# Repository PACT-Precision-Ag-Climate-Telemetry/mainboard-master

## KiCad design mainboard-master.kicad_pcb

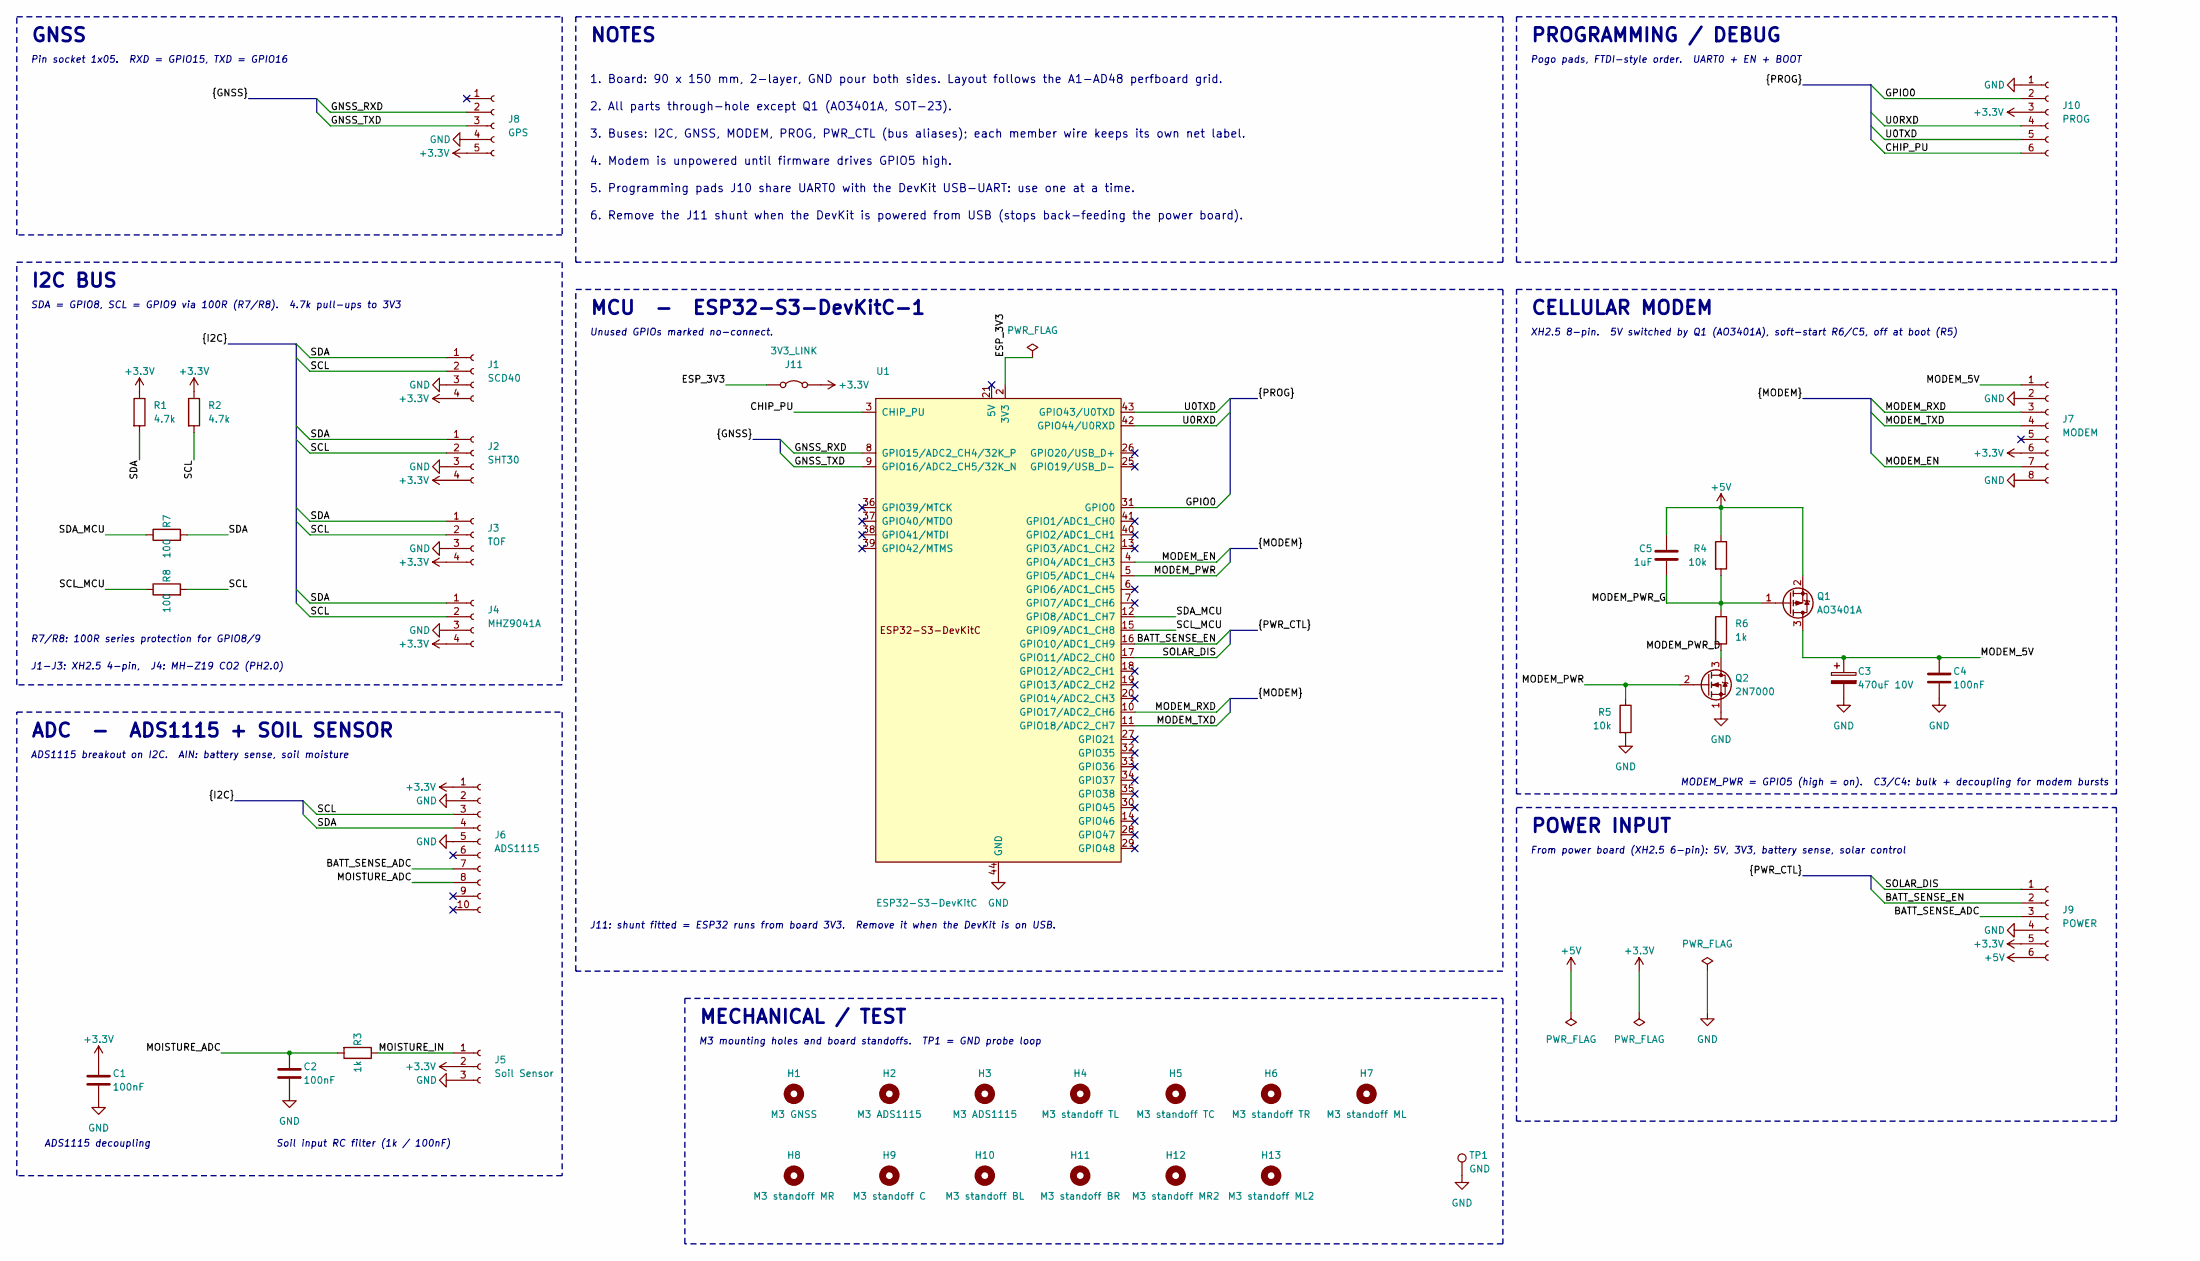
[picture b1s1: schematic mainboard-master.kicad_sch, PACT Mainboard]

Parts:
C1, C2: 100nF; C_Disc_D5.0mm_W2.5mm_P5.00mm
C3: 470uF 10V; CP_Radial_D8.0mm_P3.50mm
C4: 100nF; C_Disc_D3.0mm_W2.0mm_P2.50mm
C5: 1uF; C_Disc_D3.0mm_W2.0mm_P2.50mm
H1: M3 GNSS; MountingHole_3.2mm_M3
H2, H3: M3 ADS1115; MountingHole_3.2mm_M3
H4: M3 standoff TL; MountingHole_3.2mm_M3
H5: M3 standoff TC; MountingHole_3.2mm_M3
H6: M3 standoff TR; MountingHole_3.2mm_M3
H7: M3 standoff ML; MountingHole_3.2mm_M3
H8: M3 standoff MR; MountingHole_3.2mm_M3
H9: M3 standoff C; MountingHole_3.2mm_M3
H10: M3 standoff BL; MountingHole_3.2mm_M3
H11: M3 standoff BR; MountingHole_3.2mm_M3
H12: M3 standoff MR2; MountingHole_3.2mm_M3
H13: M3 standoff ML2; MountingHole_3.2mm_M3
J1: SCD40; JST_XH_B4B-XH-A_1x04_P2.50mm_Vertical
J2: SHT30; JST_XH_B4B-XH-A_1x04_P2.50mm_Vertical
J3: TOF; JST_XH_B4B-XH-A_1x04_P2.50mm_Vertical
J4: MHZ9041A; JST_PH_B4B-PH-K_1x04_P2.00mm_Vertical
J5: Soil Sensor; JST_XH_B3B-XH-A_1x03_P2.50mm_Vertical
J6: ADS1115; PinSocket_1x10_P2.54mm_Vertical
J7: MODEM; JST_XH_B8B-XH-A_1x08_P2.50mm_Vertical
J8: GPS; PinSocket_1x05_P2.54mm_Vertical
J9: POWER; JST_XH_B6B-XH-A_1x06_P2.50mm_Vertical
J10: PROG; PinHeader_1x06_P2.54mm_Vertical
J11: 3V3_LINK; PinHeader_1x02_P2.54mm_Vertical
Q1: AO3401A; SOT-23
Q2: 2N7000; TO-92_Inline_Wide
R1, R2: 4.7k; R_Axial_DIN0207_L6.3mm_D2.5mm_P10.16mm_Horizontal
R3: 1k; R_Axial_DIN0207_L6.3mm_D2.5mm_P10.16mm_Horizontal
R4, R5: 10k; R_Axial_DIN0207_L6.3mm_D2.5mm_P10.16mm_Horizontal
R6: 1k; R_Axial_DIN0207_L6.3mm_D2.5mm_P2.54mm_Vertical
R7, R8: 100; R_Axial_DIN0207_L6.3mm_D2.5mm_P2.54mm_Vertical
TP1: GND; TestPoint_Keystone_5000-5004_Miniature
U1: ESP32-S3-DevKitC

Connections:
+3.3V: C1.1, J1.4, J2.4, J3.4, J4.4, J5.2, J6.1, J7.6, J8.5, J9.5, J10.3, J11.2 (B), R1.1, R2.1
+5V: C5.1, J9.6, Q1.2 (S), R4.1
/BATT_SENSE_ADC: J6.7, J9.3
/BATT_SENSE_EN: J9.2, U1.16 (GPIO10/ADC1_CH9)
/CHIP_PU: J10.6, U1.3 (CHIP_PU)
/ESP_3V3: J11.1 (A), U1.1 (3V3), U1.2 (3V3)
/GNSS_RXD: J8.2, U1.8 (GPIO15/ADC2_CH4/32K_P)
/GNSS_TXD: J8.3, U1.9 (GPIO16/ADC2_CH5/32K_N)
/GPIO0: J10.2, U1.31 (GPIO0)
/MODEM_5V: C3.1, C4.1, J7.1, Q1.3 (D)
/MODEM_EN: J7.7, U1.4 (GPIO4/ADC1_CH3)
/MODEM_PWR: Q2.2 (G), R5.1, U1.5 (GPIO5/ADC1_CH4)
/MODEM_PWR_D: Q2.3 (D), R6.2
/MODEM_PWR_G: C5.2, Q1.1 (G), R4.2, R6.1
/MODEM_RXD: J7.3, U1.10 (GPIO17/ADC2_CH6)
/MODEM_TXD: J7.4, U1.11 (GPIO18/ADC2_CH7)
/MOISTURE_ADC: C2.1, J6.8, R3.2
/MOISTURE_IN: J5.1, R3.1
/SCL: J1.2, J2.2, J3.2, J4.2, J6.3, R2.2, R8.2
/SCL_MCU: R8.1, U1.15 (GPIO9/ADC1_CH8)
/SDA: J1.1, J2.1, J3.1, J4.1, J6.4, R1.2, R7.2
/SDA_MCU: R7.1, U1.12 (GPIO8/ADC1_CH7)
/SOLAR_DIS: J9.1, U1.17 (GPIO11/ADC2_CH0)
/U0RXD: J10.4, U1.42 (GPIO44/U0RXD)
/U0TXD: J10.5, U1.43 (GPIO43/U0TXD)
GND: C1.2, C2.2, C3.2, C4.2, J1.3, J2.3, J3.3, J4.3, J5.3, J6.2, J6.5, J7.2, J7.8, J8.4, J9.4, J10.1, Q2.1 (S), R5.2, TP1.1 (1_1), U1.22 (GND), U1.23 (GND), U1.24 (GND), U1.44 (GND)

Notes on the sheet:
MCU - ESP32-S3-DevKitC-1
4. Modem is unpowered until firmware drives GPIO5 high.
2. All parts through-hole except Q1 (AO3401A, SOT-23).
3. Buses: I2C, GNSS, MODEM, PROG, PWR_CTL (bus aliases); each member wire keeps its own net label.
5. Programming pads J10 share UART0 with the DevKit USB-UART: use one at a time.
M3 mounting holes and board standoffs. TP1 = GND probe loop
PROGRAMMING / DEBUG
J1-J3: XH2.5 4-pin, J4: MH-Z19 CO2 (PH2.0)
Soil input RC filter (1k / 100nF)
MODEM_PWR = GPIO5 (high = on). C3/C4: bulk + decoupling for modem bursts
1. Board: 90 x 150 mm, 2-layer, GND pour both sides. Layout follows the A1-AD48 perfboard grid.
CELLULAR MODEM
I2C BUS
Unused GPIOs marked no-connect.
ADS1115 decoupling
R7/R8: 100R series protection for GPIO8/9
POWER INPUT
GNSS
J11: shunt fitted = ESP32 runs from board 3V3. Remove it when the DevKit is on USB.
ADC - ADS1115 + SOIL SENSOR
MECHANICAL / TEST
Pin socket 1x05. RXD = GPIO15, TXD = GPIO16
SDA = GPIO8, SCL = GPIO9 via 100R (R7/R8). 4.7k pull-ups to 3V3
6. Remove the J11 shunt when the DevKit is powered from USB (stops back-feeding the power board).
NOTES
XH2.5 8-pin. 5V switched by Q1 (AO3401A), soft-start R6/C5, off at boot (R5)
ADS1115 breakout on I2C. AIN: battery sense, soil moisture
From power board (XH2.5 6-pin): 5V, 3V3, battery sense, solar control
Pogo pads, FTDI-style order. UART0 + EN + BOOT

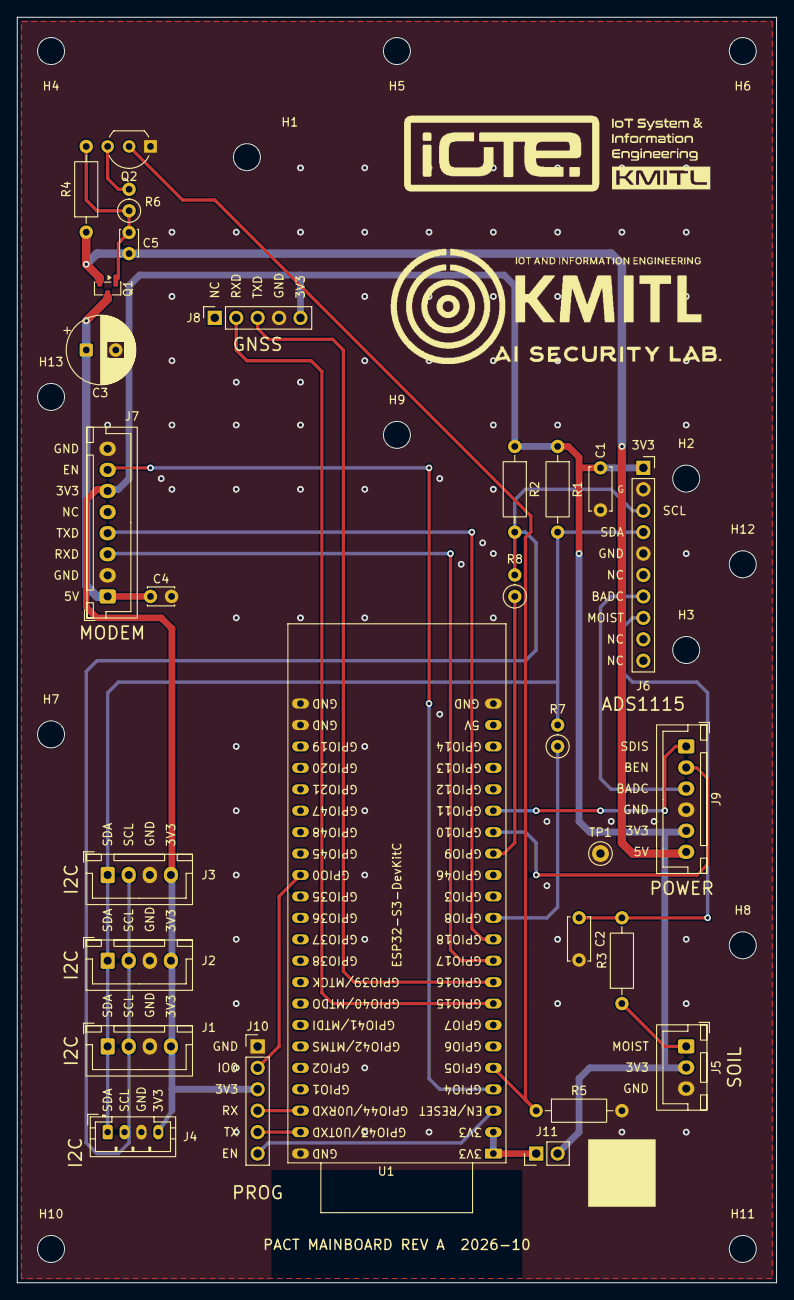
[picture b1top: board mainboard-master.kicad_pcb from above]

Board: 2 copper layers, 90.0 x 150.0 mm, 41 parts (0 on the bottom side), 26 nets.
